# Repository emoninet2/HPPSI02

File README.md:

# HPPSI02

link to [HPPSI01](https://github.com/emoninet2/HPPSI01/tree/master)

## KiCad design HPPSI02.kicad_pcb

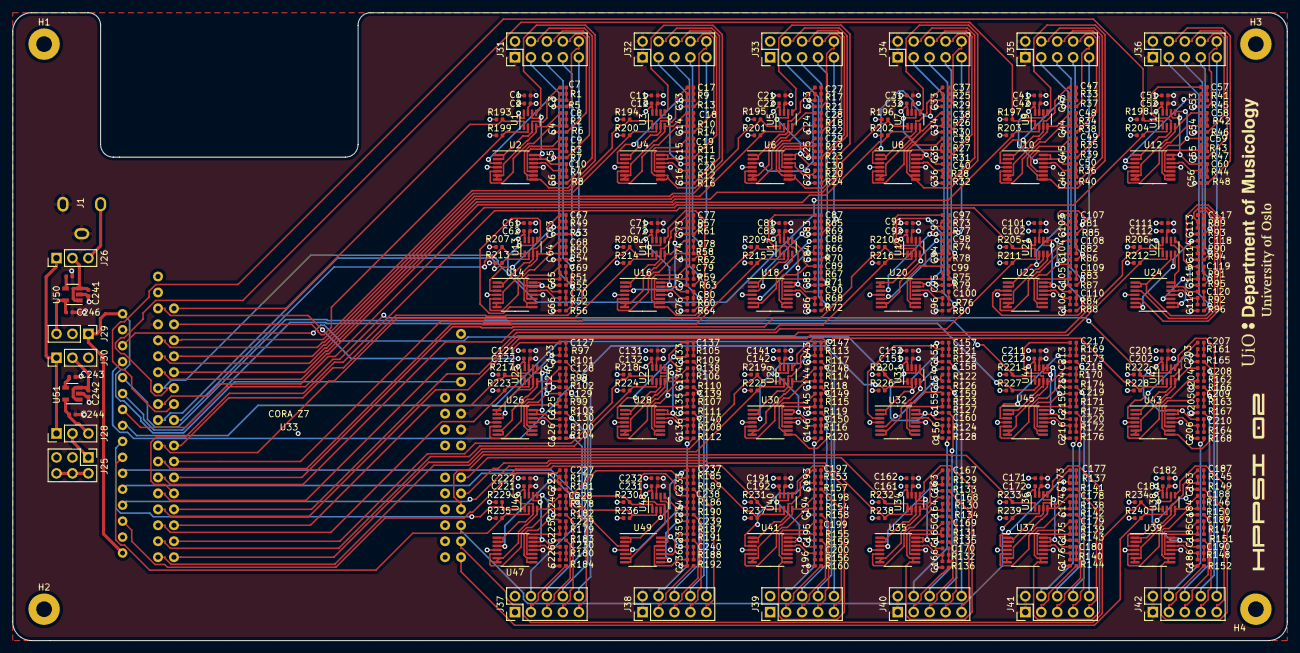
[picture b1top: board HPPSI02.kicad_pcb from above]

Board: 4 copper layers, 203.0 x 100.0 mm, 559 parts (0 on the bottom side), 445 nets.

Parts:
C1, C11, C21, C31, C41, C51, C61, C71, C81, C91, C101, C111, C121, C131, C141, C151, C161, C171, C181, C191, C201, C211, C221, C231, C244, C246: 10uF; C_0402_1005Metric
C2, C12, C22, C32, C42, C52, C62, C72, C82, C92, C102, C112, C122, C132, C142, C152, C162, C172, C182, C192, C202, C212, C222, C232: 0.1uF; C_0402_1005Metric
C3, C4, C5, C6, C13, C14, C15, C16, C23, C24, C25, C26, C33, C34, C35, C36, C43, C44, C45, C46, C53, C54, C55, C56, C63, C64, C65, C66, C73, C74, C75, C76, C83, C84, C85, C86, C93, C94, C95, C96, C103, C104, C105, C106, C113, C114, C115, C116, C123, C124, C125, C126, C133, C134, C135, C136, C143, C144, C145, C146, C153, C154, C155, C156, C163, C164, C165, C166, C173, C174, C175, C176, C183, C184, C185, C186, C193, C194, C195, C196, C203, C204, C205, C206, C213, C214, C215, C216, C223, C224, C225, C226, C233, C234, C235, C236: 220pF; C_0402_1005Metric
C7, C8, C9, C10, C17, C18, C19, C20, C27, C28, C29, C30, C37, C38, C39, C40, C47, C48, C49, C50, C57, C58, C59, C60, C67, C68, C69, C70, C77, C78, C79, C80, C87, C88, C89, C90, C97, C98, C99, C100, C107, C108, C109, C110, C117, C118, C119, C120, C127, C128, C129, C130, C137, C138, C139, C140, C147, C148, C149, C150, C157, C158, C159, C160, C167, C168, C169, C170, C177, C178, C179, C180, C187, C188, C189, C190, C197, C198, C199, C200, C207, C208, C209, C210, C217, C218, C219, C220, C227, C228, C229, C230, C237, C238, C239, C240: 470pF; C_0402_1005Metric
C241, C242: 1uF; C_0402_1005Metric
C243, C245: 0.01uF; C_0402_1005Metric
H1, H2, H3, H4: MountingHole; MountingHole_2.5mm_Pad
J1: Barrel_Jack_Switch; FC681465P
J25: Conn_02x03_Odd_Even; PinHeader_2x03_P2.54mm_Vertical
J26, J28, J29, J30: Conn_01x03_Male; PinHeader_1x03_P2.54mm_Vertical
J31, J32, J33, J34, J35, J36, J37, J38, J39, J40, J41, J42: Conn_02x05_Top_Bottom; PinHeader_2x05_P2.54mm_Vertical
R1, R2, R3, R4, R5, R6, R7, R8, R9, R10, R11, R12, R13, R14, R15, R16, R17, R18, R19, R20, R21, R22, R23, R24, R25, R26, R27, R28, R29, R30, R31, R32, R33, R34, R35, R36, R37, R38, R39, R40, R41, R42, R43, R44, R45, R46, R47, R48, R49, R50, R51, R52, R53, R54, R55, R56, R57, R58, R59, R60, R61, R62, R63, R64, R65, R66, R67, R68, R69, R70, R71, R72, R73, R74, R75, R76, R77, R78, R79, R80, R81, R82, R83, R84, R85, R86, R87, R88, R89, R90, R91, R92, R93, R94, R95, R96, R97, R98, R99, R100, R101, R102, R103, R104, R105, R106, R107, R108, R109, R110, R111, R112, R113, R114, R115, R116, R117, R118, R119, R120, R121, R122, R123, R124, R125, R126, R127, R128, R129, R130, R131, R132, R133, R134, R135, R136, R137, R138, R139, R140, R141, R142, R143, R144, R145, R146, R147, R148, R149, R150, R151, R152, R153, R154, R155, R156, R157, R158, R159, R160, R161, R162, R163, R164, R165, R166, R167, R168, R169, R170, R171, R172, R173, R174, R175, R176, R177, R178, R179, R180, R181, R182, R183, R184, R185, R186, R187, R188, R189, R190, R191, R192: 10K; R_0402_1005Metric
R193, R194, R195, R196, R197, R198, R199, R200, R201, R202, R203, R204, R205, R206, R207, R208, R209, R210, R211, R212, R213, R214, R215, R216, R217, R218, R219, R220, R221, R222, R223, R224, R225, R226, R227, R228, R229, R230, R231, R232, R233, R234, R235, R236, R237, R238, R239, R240: 1K; R_0402_1005Metric
U1, U3, U5, U7, U9, U11, U13, U15, U17, U19, U21, U23, U25, U27, U29, U31, U34, U36, U38, U40, U42, U44, U46, U48: AD7991YRJZ-1500RL7; SOT-23-8
U2, U4, U6, U8, U10, U12, U14, U16, U18, U20, U22, U24, U26, U28, U30, U32, U35, U37, U39, U41, U43, U45, U47, U49: AD8608ARZ-SOIC127P600X175-14N; TSSOP-14_4.4x5mm_P0.65mm
U33: Digilent-CoraZ7; CoraZ7_stack
U50: TPS79330-EP; SOT-23-5
U51: TPS73150DBV; SOT-23-5

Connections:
3V3_CoraZ7: J29.1, U33.55, U33.59, U33.74
3V3_Reg: C246.1, J29.3, U50.5
5V_CoraZ7: J26.1, J28.1, J30.1, U33.54
5V_Reg: C244.1, J28.3, U51.5
+3V3: C1.1, C2.1, C11.1, C12.1, C21.1, C22.1, C31.1, C32.1, C41.1, C42.1, C51.1, C52.1, C61.1, C62.1, C71.1, C72.1, C81.1, C82.1, C91.1, C92.1, C101.1, C102.1, C111.1, C112.1, C121.1, C122.1, C131.1, C132.1, C141.1, C142.1, C151.1, C152.1, C161.1, C162.1, C171.1, C172.1, C181.1, C182.1, C191.1, C192.1, C201.1, C202.1, C211.1, C212.1, C221.1, C222.1, C231.1, C232.1, J25.3, J29.2, R193.1, R194.1, R195.1, R196.1, R197.1, R198.1, R199.1, R200.1, R201.1, R202.1, R203.1, R204.1, R205.1, R206.1, R207.1, R208.1, R209.1, R210.1, R211.1, R212.1, R213.1, R214.1, R215.1, R216.1, R217.1, R218.1, R219.1, R220.1, R221.1, R222.1, R223.1, R224.1, R225.1, R226.1, R227.1, R228.1, R229.1, R230.1, R231.1, R232.1, R233.1, R234.1, R235.1, R236.1, R237.1, R238.1, R239.1, R240.1, U1.8, U3.8, U5.8, U7.8, U9.8, U11.8, U13.8, U15.8, U17.8, U19.8, U21.8, U23.8, U25.8, U27.8, U29.8, U31.8, U34.8, U36.8, U38.8, U40.8, U42.8, U44.8, U46.8, U48.8
+5V: J25.1, J28.2
GND: C1.2, C2.2, C3.2, C4.2, C5.2, C6.2, C11.2, C12.2, C13.2, C14.2, C15.2, C16.2, C21.2, C22.2, C23.2, C24.2, C25.2, C26.2, C31.2, C32.2, C33.2, C34.2, C35.2, C36.2, C41.2, C42.2, C43.2, C44.2, C45.2, C46.2, C51.2, C52.2, C53.2, C54.2, C55.2, C56.2, C61.2, C62.2, C63.2, C64.2, C65.2, C66.2, C71.2, C72.2, C73.2, C74.2, C75.2, C76.2, C81.2, C82.2, C83.2, C84.2, C85.2, C86.2, C91.2, C92.2, C93.2, C94.2, C95.2, C96.2, C101.2, C102.2, C103.2, C104.2, C105.2, C106.2, C111.2, C112.2, C113.2, C114.2, C115.2, C116.2, C121.2, C122.2, C123.2, C124.2, C125.2, C126.2, C131.2, C132.2, C133.2, C134.2, C135.2, C136.2, C141.2, C142.2, C143.2, C144.2, C145.2, C146.2, C151.2, C152.2, C153.2, C154.2, C155.2, C156.2, C161.2, C162.2, C163.2, C164.2, C165.2, C166.2, C171.2, C172.2, C173.2, C174.2, C175.2, C176.2, C181.2, C182.2, C183.2, C184.2, C185.2, C186.2, C191.2, C192.2, C193.2, C194.2, C195.2, C196.2, C201.2, C202.2, C203.2, C204.2, C205.2, C206.2, C211.2, C212.2, C213.2, C214.2, C215.2, C216.2, C221.2, C222.2, C223.2, C224.2, C225.2, C226.2, C231.2, C232.2, C233.2, C234.2, C235.2, C236.2, C241.2, C242.2, C243.2, C244.2, C245.2, C246.2, J1.2, J1.3, J31.1, J31.2, J32.1, J32.2, J34.1, J34.2, J35.1, J35.2, J36.1, J36.2, J37.1, J37.2, J38.1, J38.2, J40.1, J40.2, J41.1, J41.2, J42.1, J42.2, U1.7, U2.11, U3.7, U4.11, U5.7, U6.11, U7.7, U8.11, U9.7, U10.11, U11.7, U12.11, U13.7, U14.11, U15.7, U16.11, U17.7, U18.11, U19.7, U20.11, U21.7, U22.11, U23.7, U24.11, U25.7, U26.11, U27.7, U28.11, U29.7, U30.11, U31.7, U32.11, U33.15, U33.52, U33.53, U33.60, U33.73, U34.7, U35.11, U36.7, U37.11, U38.7, U39.11, U40.7, U41.11, U42.7, U43.11, U44.7, U45.11, U46.7, U47.11, U48.7, U49.11, U50.2, U51.2
unnamed: C3.1, R1.2, U2.3
unnamed: C4.1, R2.2, U2.5
unnamed: C5.1, R3.2, U2.10
unnamed: C6.1, R4.2, U2.12
unnamed: C7.1, U1.3, U2.1, U2.2
unnamed: C7.2, R1.1, R5.2
unnamed: C8.1, U1.4, U2.6, U2.7
unnamed: C8.2, R2.1, R6.2
unnamed: C9.1, U1.5, U2.8, U2.9
unnamed: C9.2, R3.1, R7.2
unnamed: C10.1, U1.6, U2.13, U2.14
unnamed: C10.2, R4.1, R8.2
unnamed: C13.1, R9.2, U4.3
unnamed: C14.1, R10.2, U4.5
unnamed: C15.1, R11.2, U4.10
unnamed: C16.1, R12.2, U4.12
unnamed: C17.1, U3.3, U4.1, U4.2
unnamed: C17.2, R9.1, R13.2
unnamed: C18.1, U3.4, U4.6, U4.7
unnamed: C18.2, R10.1, R14.2
unnamed: C19.1, U3.5, U4.8, U4.9
unnamed: C19.2, R11.1, R15.2
unnamed: C20.1, U3.6, U4.13, U4.14
unnamed: C20.2, R12.1, R16.2
unnamed: C23.1, R17.2, U6.3
unnamed: C24.1, R18.2, U6.5
unnamed: C25.1, R19.2, U6.10
unnamed: C26.1, R20.2, U6.12
unnamed: C27.1, U5.3, U6.1, U6.2
unnamed: C27.2, R17.1, R21.2
unnamed: C28.1, U5.4, U6.6, U6.7
unnamed: C28.2, R18.1, R22.2
unnamed: C29.1, U5.5, U6.8, U6.9
unnamed: C29.2, R19.1, R23.2
unnamed: C30.1, U5.6, U6.13, U6.14
unnamed: C30.2, R20.1, R24.2
unnamed: C33.1, R25.2, U8.3
unnamed: C34.1, R26.2, U8.5
unnamed: C35.1, R27.2, U8.10
unnamed: C36.1, R28.2, U8.12
unnamed: C37.1, U7.3, U8.1, U8.2
unnamed: C37.2, R25.1, R29.2
unnamed: C38.1, U7.4, U8.6, U8.7
unnamed: C38.2, R26.1, R30.2
unnamed: C39.1, U7.5, U8.8, U8.9
unnamed: C39.2, R27.1, R31.2
unnamed: C40.1, U7.6, U8.13, U8.14
unnamed: C40.2, R28.1, R32.2
unnamed: C43.1, R33.2, U10.3
unnamed: C44.1, R34.2, U10.5
unnamed: C45.1, R35.2, U10.10
unnamed: C46.1, R36.2, U10.12
unnamed: C47.1, U9.3, U10.1, U10.2
unnamed: C47.2, R33.1, R37.2
unnamed: C48.1, U9.4, U10.6, U10.7
unnamed: C48.2, R34.1, R38.2
unnamed: C49.1, U9.5, U10.8, U10.9
unnamed: C49.2, R35.1, R39.2
unnamed: C50.1, U9.6, U10.13, U10.14
unnamed: C50.2, R36.1, R40.2
unnamed: C53.1, R41.2, U12.3
unnamed: C54.1, R42.2, U12.5
unnamed: C55.1, R43.2, U12.10
unnamed: C56.1, R44.2, U12.12
unnamed: C57.1, U11.3, U12.1, U12.2
unnamed: C57.2, R41.1, R45.2
unnamed: C58.1, U11.4, U12.6, U12.7
unnamed: C58.2, R42.1, R46.2
unnamed: C59.1, U11.5, U12.8, U12.9
unnamed: C59.2, R43.1, R47.2
unnamed: C60.1, U11.6, U12.13, U12.14
unnamed: C60.2, R44.1, R48.2
unnamed: C63.1, R49.2, U14.3
unnamed: C64.1, R50.2, U14.5
unnamed: C65.1, R51.2, U14.10
unnamed: C66.1, R52.2, U14.12
unnamed: C67.1, U13.3, U14.1, U14.2
unnamed: C67.2, R49.1, R53.2
unnamed: C68.1, U13.4, U14.6, U14.7
unnamed: C68.2, R50.1, R54.2
unnamed: C69.1, U13.5, U14.8, U14.9
unnamed: C69.2, R51.1, R55.2
unnamed: C70.1, U13.6, U14.13, U14.14
unnamed: C70.2, R52.1, R56.2
unnamed: C73.1, R57.2, U16.3
unnamed: C74.1, R58.2, U16.5
unnamed: C75.1, R59.2, U16.10
unnamed: C76.1, R60.2, U16.12
unnamed: C77.1, U15.3, U16.1, U16.2
unnamed: C77.2, R57.1, R61.2
unnamed: C78.1, U15.4, U16.6, U16.7
unnamed: C78.2, R58.1, R62.2
unnamed: C79.1, U15.5, U16.8, U16.9
unnamed: C79.2, R59.1, R63.2
unnamed: C80.1, U15.6, U16.13, U16.14
unnamed: C80.2, R60.1, R64.2
unnamed: C83.1, R65.2, U18.3
unnamed: C84.1, R66.2, U18.5
unnamed: C85.1, R67.2, U18.10
unnamed: C86.1, R68.2, U18.12
unnamed: C87.1, U17.3, U18.1, U18.2
unnamed: C87.2, R65.1, R69.2
unnamed: C88.1, U17.4, U18.6, U18.7
unnamed: C88.2, R66.1, R70.2
unnamed: C89.1, U17.5, U18.8, U18.9
unnamed: C89.2, R67.1, R71.2
unnamed: C90.1, U17.6, U18.13, U18.14
unnamed: C90.2, R68.1, R72.2
unnamed: C93.1, R73.2, U20.3
unnamed: C94.1, R74.2, U20.5
unnamed: C95.1, R75.2, U20.10
unnamed: C96.1, R76.2, U20.12
unnamed: C97.1, U19.3, U20.1, U20.2
unnamed: C97.2, R73.1, R77.2
unnamed: C98.1, U19.4, U20.6, U20.7
unnamed: C98.2, R74.1, R78.2
unnamed: C99.1, U19.5, U20.8, U20.9
unnamed: C99.2, R75.1, R79.2
unnamed: C100.1, U19.6, U20.13, U20.14
unnamed: C100.2, R76.1, R80.2
unnamed: C103.1, R81.2, U22.3
unnamed: C104.1, R82.2, U22.5
unnamed: C105.1, R83.2, U22.10
unnamed: C106.1, R84.2, U22.12
unnamed: C107.1, U21.3, U22.1, U22.2
unnamed: C107.2, R81.1, R85.2
unnamed: C108.1, U21.4, U22.6, U22.7
unnamed: C108.2, R82.1, R86.2
unnamed: C109.1, U21.5, U22.8, U22.9
unnamed: C109.2, R83.1, R87.2
unnamed: C110.1, U21.6, U22.13, U22.14
unnamed: C110.2, R84.1, R88.2
unnamed: C113.1, R89.2, U24.3
unnamed: C114.1, R90.2, U24.5
unnamed: C115.1, R91.2, U24.10
unnamed: C116.1, R92.2, U24.12
unnamed: C117.1, U23.3, U24.1, U24.2
unnamed: C117.2, R89.1, R93.2
unnamed: C118.1, U23.4, U24.6, U24.7
unnamed: C118.2, R90.1, R94.2
unnamed: C119.1, U23.5, U24.8, U24.9
unnamed: C119.2, R91.1, R95.2
unnamed: C120.1, U23.6, U24.13, U24.14
unnamed: C120.2, R92.1, R96.2
unnamed: C123.1, R97.2, U26.3
unnamed: C124.1, R98.2, U26.5
unnamed: C125.1, R99.2, U26.10
unnamed: C126.1, R100.2, U26.12
unnamed: C127.1, U25.3, U26.1, U26.2
unnamed: C127.2, R97.1, R101.2
unnamed: C128.1, U25.4, U26.6, U26.7
unnamed: C128.2, R98.1, R102.2
unnamed: C129.1, U25.5, U26.8, U26.9
unnamed: C129.2, R99.1, R103.2
unnamed: C130.1, U25.6, U26.13, U26.14
unnamed: C130.2, R100.1, R104.2
unnamed: C133.1, R105.2, U28.3
unnamed: C134.1, R106.2, U28.5
unnamed: C135.1, R107.2, U28.10
unnamed: C136.1, R108.2, U28.12
unnamed: C137.1, U27.3, U28.1, U28.2
unnamed: C137.2, R105.1, R109.2
unnamed: C138.1, U27.4, U28.6, U28.7
unnamed: C138.2, R106.1, R110.2
unnamed: C139.1, U27.5, U28.8, U28.9
unnamed: C139.2, R107.1, R111.2
unnamed: C140.1, U27.6, U28.13, U28.14
unnamed: C140.2, R108.1, R112.2
unnamed: C143.1, R113.2, U30.3
unnamed: C144.1, R114.2, U30.5
unnamed: C145.1, R115.2, U30.10
unnamed: C146.1, R116.2, U30.12
unnamed: C147.1, U29.3, U30.1, U30.2
unnamed: C147.2, R113.1, R117.2
unnamed: C148.1, U29.4, U30.6, U30.7
unnamed: C148.2, R114.1, R118.2
unnamed: C149.1, U29.5, U30.8, U30.9
unnamed: C149.2, R115.1, R119.2
unnamed: C150.1, U29.6, U30.13, U30.14
unnamed: C150.2, R116.1, R120.2
unnamed: C153.1, R121.2, U32.3
unnamed: C154.1, R122.2, U32.5
unnamed: C155.1, R123.2, U32.10
unnamed: C156.1, R124.2, U32.12
unnamed: C157.1, U31.3, U32.1, U32.2
unnamed: C157.2, R121.1, R125.2
unnamed: C158.1, U31.4, U32.6, U32.7
unnamed: C158.2, R122.1, R126.2
unnamed: C159.1, U31.5, U32.8, U32.9
unnamed: C159.2, R123.1, R127.2
unnamed: C160.1, U31.6, U32.13, U32.14
unnamed: C160.2, R124.1, R128.2
unnamed: C163.1, R129.2, U35.3
unnamed: C164.1, R130.2, U35.5
unnamed: C165.1, R131.2, U35.10
unnamed: C166.1, R132.2, U35.12
unnamed: C167.1, U34.3, U35.1, U35.2
unnamed: C167.2, R129.1, R133.2
unnamed: C168.1, U34.4, U35.6, U35.7
unnamed: C168.2, R130.1, R134.2
unnamed: C169.1, U34.5, U35.8, U35.9
unnamed: C169.2, R131.1, R135.2
unnamed: C170.1, U34.6, U35.13, U35.14
unnamed: C170.2, R132.1, R136.2
unnamed: C173.1, R137.2, U37.3
unnamed: C174.1, R138.2, U37.5
unnamed: C175.1, R139.2, U37.10
unnamed: C176.1, R140.2, U37.12
unnamed: C177.1, U36.3, U37.1, U37.2
unnamed: C177.2, R137.1, R141.2
unnamed: C178.1, U36.4, U37.6, U37.7
unnamed: C178.2, R138.1, R142.2
unnamed: C179.1, U36.5, U37.8, U37.9
unnamed: C179.2, R139.1, R143.2
unnamed: C180.1, U36.6, U37.13, U37.14
unnamed: C180.2, R140.1, R144.2
unnamed: C183.1, R145.2, U39.3
unnamed: C184.1, R146.2, U39.5
unnamed: C185.1, R147.2, U39.10
unnamed: C186.1, R148.2, U39.12
unnamed: C187.1, U38.3, U39.1, U39.2
unnamed: C187.2, R145.1, R149.2
unnamed: C188.1, U38.4, U39.6, U39.7
unnamed: C188.2, R146.1, R150.2
unnamed: C189.1, U38.5, U39.8, U39.9
unnamed: C189.2, R147.1, R151.2
unnamed: C190.1, U38.6, U39.13, U39.14
unnamed: C190.2, R148.1, R152.2
unnamed: C193.1, R153.2, U41.3
unnamed: C194.1, R154.2, U41.5
unnamed: C195.1, R155.2, U41.10
unnamed: C196.1, R156.2, U41.12
unnamed: C197.1, U40.3, U41.1, U41.2
unnamed: C197.2, R153.1, R157.2
unnamed: C198.1, U40.4, U41.6, U41.7
unnamed: C198.2, R154.1, R158.2
unnamed: C199.1, U40.5, U41.8, U41.9
unnamed: C199.2, R155.1, R159.2
unnamed: C200.1, U40.6, U41.13, U41.14
unnamed: C200.2, R156.1, R160.2
unnamed: C203.1, R161.2, U43.3
unnamed: C204.1, R162.2, U43.5
unnamed: C205.1, R163.2, U43.10
unnamed: C206.1, R164.2, U43.12
unnamed: C207.1, U42.3, U43.1, U43.2
unnamed: C207.2, R161.1, R165.2
unnamed: C208.1, U42.4, U43.6, U43.7
unnamed: C208.2, R162.1, R166.2
unnamed: C209.1, U42.5, U43.8, U43.9
unnamed: C209.2, R163.1, R167.2
unnamed: C210.1, U42.6, U43.13, U43.14
unnamed: C210.2, R164.1, R168.2
unnamed: C213.1, R169.2, U45.3
unnamed: C214.1, R170.2, U45.5
unnamed: C215.1, R171.2, U45.10
unnamed: C216.1, R172.2, U45.12
unnamed: C217.1, U44.3, U45.1, U45.2
unnamed: C217.2, R169.1, R173.2
unnamed: C218.1, U44.4, U45.6, U45.7
unnamed: C218.2, R170.1, R174.2
unnamed: C219.1, U44.5, U45.8, U45.9
unnamed: C219.2, R171.1, R175.2
unnamed: C220.1, U44.6, U45.13, U45.14
unnamed: C220.2, R172.1, R176.2
unnamed: C223.1, R177.2, U47.3
unnamed: C224.1, R178.2, U47.5
unnamed: C225.1, R179.2, U47.10
unnamed: C226.1, R180.2, U47.12
unnamed: C227.1, U46.3, U47.1, U47.2
unnamed: C227.2, R177.1, R181.2
unnamed: C228.1, U46.4, U47.6, U47.7
unnamed: C228.2, R178.1, R182.2
unnamed: C229.1, U46.5, U47.8, U47.9
unnamed: C229.2, R179.1, R183.2
unnamed: C230.1, U46.6, U47.13, U47.14
unnamed: C230.2, R180.1, R184.2
unnamed: C233.1, R185.2, U49.3
unnamed: C234.1, R186.2, U49.5
unnamed: C235.1, R187.2, U49.10
unnamed: C236.1, R188.2, U49.12
unnamed: C237.1, U48.3, U49.1, U49.2
unnamed: C237.2, R185.1, R189.2
unnamed: C238.1, U48.4, U49.6, U49.7
unnamed: C238.2, R186.1, R190.2
unnamed: C239.1, U48.5, U49.8, U49.9
unnamed: C239.2, R187.1, R191.2
unnamed: C240.1, U48.6, U49.13, U49.14
unnamed: C240.2, R188.1, R192.2
unnamed: C241.1, J26.2, U50.1, U50.3
unnamed: C242.1, J30.2, U51.1, U51.3
unnamed: C243.1, U51.4
unnamed: C245.1, U50.4
SCL0: R199.2, U1.2, U33.33
SCL1: R200.2, U3.2, U33.14
SCL2: R201.2, U5.2, U33.13
SCL3: R202.2, U7.2, U33.12
SCL4: R203.2, U9.2, U33.11
SCL5: R204.2, U11.2, U33.10
SCL6: R213.2, U13.2, U33.9
SCL7: R214.2, U15.2, U33.8
SCL8: R215.2, U17.2, U33.7
SCL9: R216.2, U19.2, U33.6
SCL10: R211.2, U21.2, U33.5
SCL11: R212.2, U23.2, U33.4
SCL12: R223.2, U25.2, U33.3
SCL13: R224.2, U27.2, U33.2
SCL14: R225.2, U29.2, U33.1
SCL15: R226.2, U31.2, U33.71
SCL16: R227.2, U33.69, U44.2
SCL17: R228.2, U33.67, U42.2
SCL18: R235.2, U33.65, U46.2
SCL19: R236.2, U33.63, U48.2
SCL20: R237.2, U33.61, U40.2
SCL21: R238.2, U33.49, U34.2
SCL22: R239.2, U33.47, U36.2
SCL23: R240.2, U33.45, U38.2
SDA0: R193.2, U1.1, U33.34
SDA1: R194.2, U3.1, U33.32
SDA2: R195.2, U5.1, U33.31
SDA3: R196.2, U7.1, U33.30
SDA4: R197.2, U9.1, U33.29
SDA5: R198.2, U11.1, U33.28
SDA6: R207.2, U13.1, U33.27
SDA7: R208.2, U15.1, U33.26
SDA8: R209.2, U17.1, U33.25
SDA9: R210.2, U19.1, U33.24
SDA10: R205.2, U21.1, U33.23
SDA11: R206.2, U23.1, U33.22
SDA12: R217.2, U25.1, U33.21
SDA13: R218.2, U27.1, U33.20
SDA14: R219.2, U29.1, U33.19
SDA15: R220.2, U31.1, U33.72
SDA16: R221.2, U33.70, U44.1
SDA17: R222.2, U33.68, U42.1
SDA18: R229.2, U33.66, U46.1
SDA19: R230.2, U33.64, U48.1
SDA20: R231.2, U33.62, U40.1
SDA21: R232.2, U33.50, U34.1
SDA22: R233.2, U33.48, U36.1
SDA23: R234.2, U33.46, U38.1
VDD_Filters: J25.2, J25.4, J25.6, U2.4, U4.4, U6.4, U8.4, U10.4, U12.4, U14.4, U16.4, U18.4, U20.4, U22.4, U24.4, U26.4, U28.4, U30.4, U32.4, U35.4, U37.4, U39.4, U41.4, U43.4, U45.4, U47.4, U49.4
VIN1_0: J31.4, R8.1
VIN1_1: J32.4, R16.1
VIN1_2: J33.4, R24.1
VIN1_3: J34.4, R32.1
VIN1_4: J35.4, R40.1
VIN1_5: J36.4, R48.1
VIN1_6: J31.3, R56.1
VIN1_7: J32.3, R64.1
VIN1_8: J33.3, R72.1
VIN1_9: J34.3, R80.1
VIN1_10: J35.3, R88.1
VIN1_11: J36.3, R96.1
VIN1_12: J37.4, R104.1
VIN1_13: J38.4, R112.1
VIN1_14: J39.4, R120.1
VIN1_15: J40.4, R128.1
VIN1_16: J41.4, R176.1
VIN1_17: J42.4, R168.1
VIN1_18: J37.3, R184.1
VIN1_19: J38.3, R192.1
VIN1_20: J39.3, R160.1
VIN1_21: J40.3, R136.1
VIN1_22: J41.3, R144.1
VIN1_23: J42.3, R152.1
VIN2_0: J31.6, R7.1
VIN2_1: J32.6, R15.1
VIN2_2: J33.6, R23.1
VIN2_3: J34.6, R31.1
VIN2_4: J35.6, R39.1
VIN2_5: J36.6, R47.1
VIN2_6: J31.5, R55.1
VIN2_7: J32.5, R63.1
VIN2_8: J33.5, R71.1
VIN2_9: J34.5, R79.1
VIN2_10: J35.5, R87.1
VIN2_11: J36.5, R95.1
VIN2_12: J37.6, R103.1
VIN2_13: J38.6, R111.1
VIN2_14: J39.6, R119.1
VIN2_15: J40.6, R127.1
VIN2_16: J41.6, R175.1
VIN2_17: J42.6, R167.1
VIN2_18: J37.5, R183.1
VIN2_19: J38.5, R191.1
VIN2_20: J39.5, R159.1
VIN2_21: J40.5, R135.1
VIN2_22: J41.5, R143.1
VIN2_23: J42.5, R151.1
VIN3_0: J31.8, R6.1
VIN3_1: J32.8, R14.1
VIN3_2: J33.8, R22.1
VIN3_3: J34.8, R30.1
VIN3_4: J35.8, R38.1
VIN3_5: J36.8, R46.1
VIN3_6: J31.7, R54.1
VIN3_7: J32.7, R62.1
VIN3_8: J33.7, R70.1
VIN3_9: J34.7, R78.1
VIN3_10: J35.7, R86.1
VIN3_11: J36.7, R94.1
VIN3_12: J37.8, R102.1
VIN3_13: J38.8, R110.1
VIN3_14: J39.8, R118.1
VIN3_15: J40.8, R126.1
VIN3_16: J41.8, R174.1
VIN3_17: J42.8, R166.1
VIN3_18: J37.7, R182.1
VIN3_19: J38.7, R190.1
VIN3_20: J39.7, R158.1
VIN3_21: J40.7, R134.1
VIN3_22: J41.7, R142.1
VIN3_23: J42.7, R150.1
VIN4_0: J31.10, R5.1
VIN4_1: J32.10, R13.1
VIN4_2: J33.10, R21.1
VIN4_3: J34.10, R29.1
VIN4_4: J35.10, R37.1
VIN4_5: J36.10, R45.1
VIN4_6: J31.9, R53.1
VIN4_7: J32.9, R61.1
VIN4_8: J33.9, R69.1
VIN4_9: J34.9, R77.1
VIN4_10: J35.9, R85.1
VIN4_11: J36.9, R93.1
VIN4_12: J37.10, R101.1
VIN4_13: J38.10, R109.1
VIN4_14: J39.10, R117.1
VIN4_15: J40.10, R125.1
VIN4_16: J41.10, R173.1
VIN4_17: J42.10, R165.1
VIN4_18: J37.9, R181.1
VIN4_19: J38.9, R189.1
VIN4_20: J39.9, R157.1
VIN4_21: J40.9, R133.1
VIN4_22: J41.9, R141.1
VIN4_23: J42.9, R149.1
V_RAW: J1.1, J26.3, J30.3

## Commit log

2020-03-05 added existing project files and folders.
2020-03-06 replaced position of decoupling capacitors
2020-03-06 added vias for direct connection to ground and 3.3V plane. Done routing for power section
2020-03-06 R191 rotated
2020-03-06 milestone: placement of components
2020-03-07 saved session from autorouter
2020-03-09 changed position of cora z7 to be at center with cutout to give headroom for ethernet and powerjack
2020-03-09 added mounting holes
2020-03-09 Pin headers have pins connected to ground
2020-03-09 added mounting hole in schematic and corresponding footprint on layout
2020-03-09 added net class for power lines
2020-03-09 updated net class
2020-03-09 added vdd_filter tracks manually on power plane
2020-03-09 changed board setting for middle layers to be power plane to avoid placing interconnect by freerouter
2020-03-10 manually routed power section. library moved internally.
2020-03-13 fixed via net near R229 and R235 to +3V3
2020-03-19 routing complete
2020-03-19 updated copper pour on top and bottom layer
2020-04-19 changed power pin to dc barrel jack
2020-05-29 added logo
2020-05-31 renamed project to HPPSI02
2020-05-31 rearranged folder naming
2024-08-25 added 3D object in wrl format
